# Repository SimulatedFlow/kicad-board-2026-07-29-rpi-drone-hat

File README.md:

# 2026-07-29-rpi-drone-hat

<!-- SF-STORE-BLOCK:BEGIN -->
## 🛒 Source-available — see before you buy

This repository contains the **full design files** of a commercial hardware board. It is **source-available, not open source**: read it, evaluate it, then buy a license to use it. See **LICENSE.md (source-available, purchase required)**.

**Get it / Buy:**
- **Order on eBay** (this board, bare PCB): https://www.ebay.de/itm/398230767491
- Product page (specs, photos, price): https://simulatedflow.teufel-engineering.com/platinen/2026-07-29-rpi-drone-hat/
- eBay store — all our boards and PCB art: https://www.ebay.de/usr/simula-9
- Merch shop (dev & gaming): https://simulatedflow.myspreadshop.de
- Merch shop (Synthetica / EDM): https://synthetica.myspreadshop.de
- Direct / invoice (Simulated Flow UG): simulatedflow@gmail.com

### 📬 **Free Board Documentation & Firmware Pack**

Schematics, BOMs and example-firmware docs for our STM32 carrier boards. Get it by joining the newsletter — plus a heads-up when something new ships. Double opt-in, unsubscribe in one click, no address sharing.

👉 **[Get the free pack](https://simulatedflow.teufel-engineering.com/newsletter/hardware/?q=gh)**

_© 2026 Simulated Flow UG. All rights reserved._
<!-- SF-STORE-BLOCK:END -->

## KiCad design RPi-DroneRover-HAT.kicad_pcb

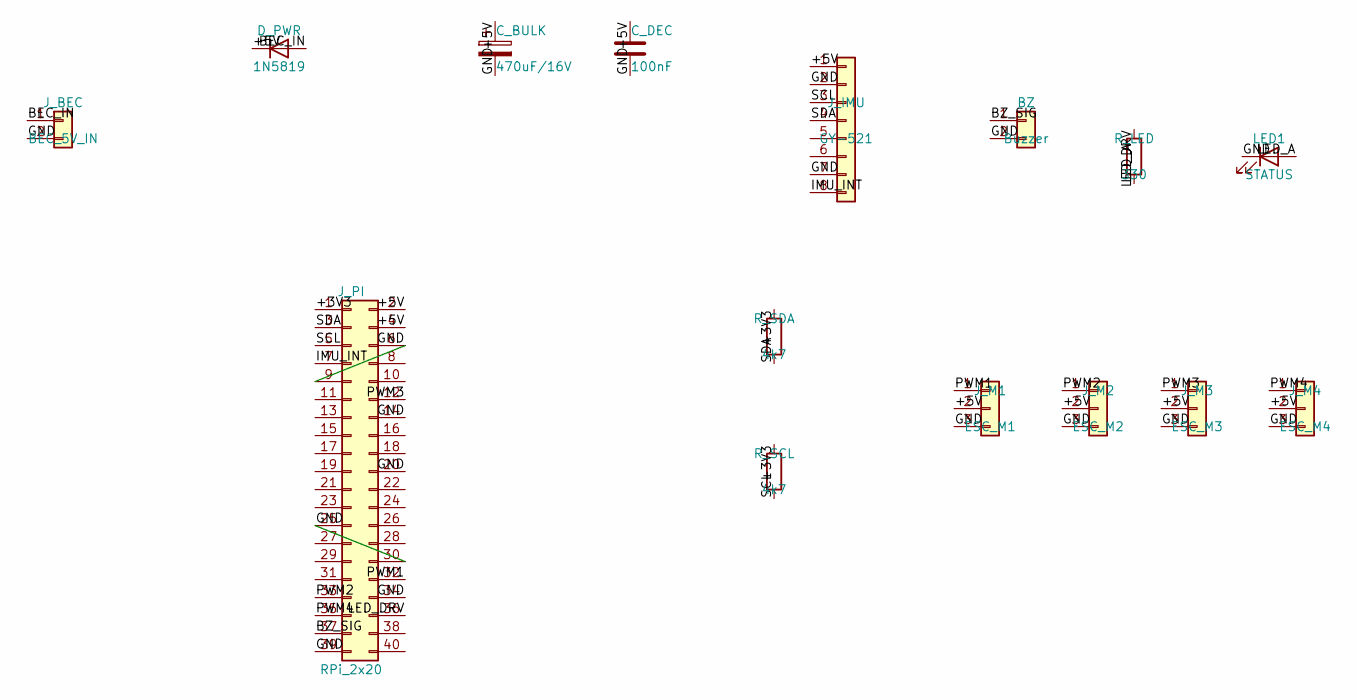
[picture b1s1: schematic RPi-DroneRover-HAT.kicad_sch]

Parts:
BZ: Buzzer; PinHeader_1x02_P2.54mm_Vertical
C_BULK: 470uF/16V; CP_Radial_D8.0mm_P3.50mm
C_DEC: 100nF; C_Disc_D3.0mm_W1.6mm_P2.50mm
D_PWR: 1N5819; D_DO-41_SOD81_P10.16mm_Horizontal
J_BEC: BEC_5V_IN; TerminalBlock_Phoenix_MKDS-1,5-2-5.08_1x02_P5.08mm_Horizont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
J_IMU: GY-521; PinSocket_1x08_P2.54mm_Vertical
J_M1: ESC_M1; PinHeader_1x03_P2.54mm_Vertical
J_M2: ESC_M2; PinHeader_1x03_P2.54mm_Vertical
J_M3: ESC_M3; PinHeader_1x03_P2.54mm_Vertical
J_M4: ESC_M4; PinHeader_1x03_P2.54mm_Vertical
J_PI: RPi_2x20; PinSocket_2x20_P2.54mm_Vertical
LED1: STATUS; LED_D5.0mm
R_LED: 330; R_Axial_DIN0207_L6.3mm_D2.5mm_P7.62mm_Horizontal
R_SCL: 4k7; R_Axial_DIN0207_L6.3mm_D2.5mm_P7.62mm_Horizontal
R_SDA: 4k7; R_Axial_DIN0207_L6.3mm_D2.5mm_P7.62mm_Horizontal

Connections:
+3V3: J_PI.1, R_SCL.1, R_SDA.1
+5V: C_BULK.1, C_DEC.1, D_PWR.1 (K), J_IMU.1, J_M1.2, J_M2.2, J_M3.2, J_M4.2, J_PI.2, J_PI.4
BEC_IN: D_PWR.2 (A), J_BEC.1
BZ_SIG: BZ.1, J_PI.37
GND: BZ.2, C_BULK.2, C_DEC.2, J_BEC.2, J_IMU.2, J_IMU.7, J_M1.3, J_M2.3, J_M3.3, J_M4.3, J_PI.6, J_PI.9, J_PI.14, J_PI.20, J_PI.25, J_PI.30, J_PI.34, J_PI.39, LED1.1 (K)
IMU_INT: J_IMU.8, J_PI.7
LED_A: LED1.2 (A), R_LED.2
LED_DRV: J_PI.36, R_LED.1
PWM1: J_M1.1, J_PI.32
PWM2: J_M2.1, J_PI.33
PWM3: J_M3.1, J_PI.12
PWM4: J_M4.1, J_PI.35
SCL: J_IMU.3, J_PI.5, R_SCL.2
SDA: J_IMU.4, J_PI.3, R_SDA.2

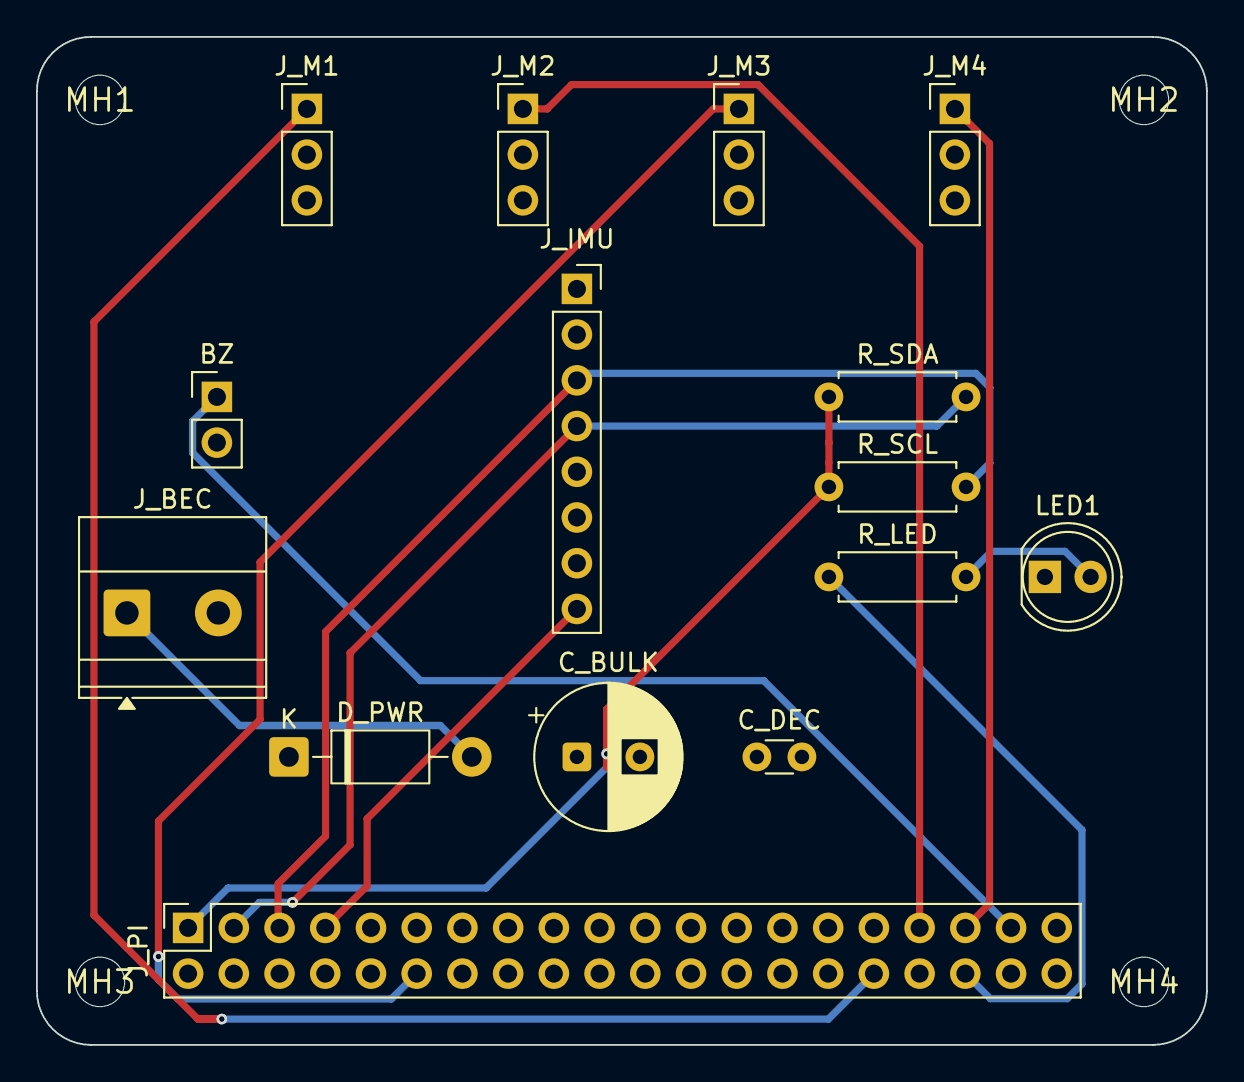
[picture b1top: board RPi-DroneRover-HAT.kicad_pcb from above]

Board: 4 copper layers, 65.0 x 56.0 mm, 19 parts (0 on the bottom side), 14 nets.

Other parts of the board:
MH1, MH2, MH3, MH4: MountingHole_2.75mm
